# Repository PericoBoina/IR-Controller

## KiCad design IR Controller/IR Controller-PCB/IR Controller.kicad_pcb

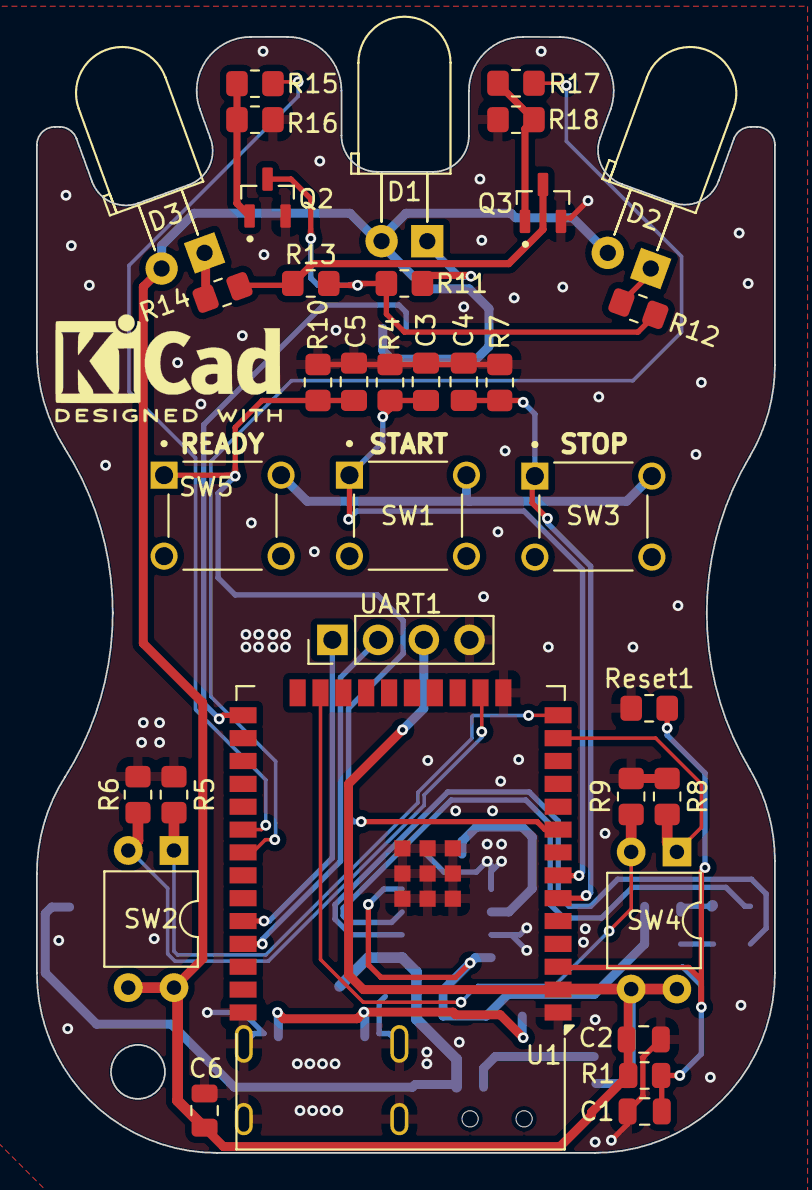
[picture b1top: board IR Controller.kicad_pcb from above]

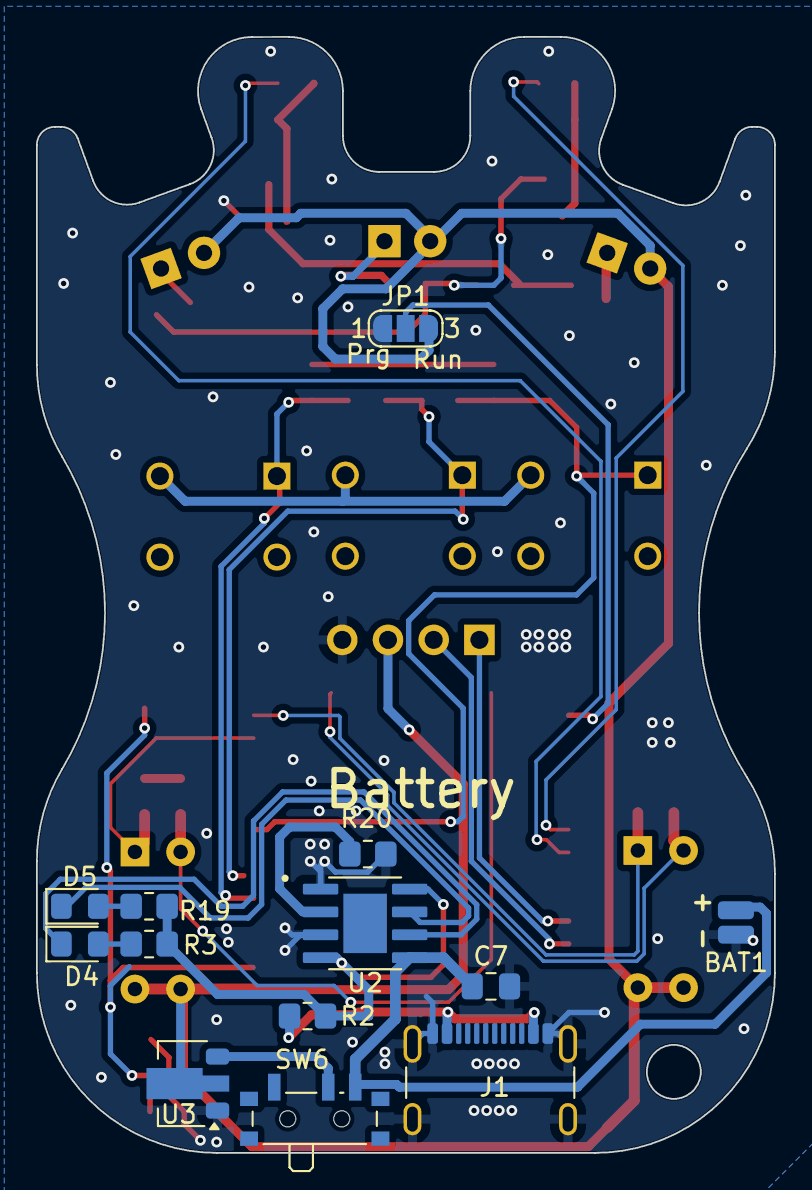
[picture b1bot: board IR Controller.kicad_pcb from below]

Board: 2 copper layers, 41.0 x 62.0 mm, 48 parts (13 on the bottom side), 32 nets.

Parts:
BAT1: 3.7V; SolderWirePad_1x01_SMD_1x2mm
C1: 0.1uF; C_0805_2012Metric
C2, C6: 1uF; C_0805_2012Metric
C3, C4, C5: 0.1uF; C_0805_2012Metric_Pad1.18x1.45mm_HandSolder
C7: 10uF; C_0805_2012Metric_Pad1.18x1.45mm_HandSolder
D1, D2, D3: LED; LED_D5.0mm_Horizontal_O3.81mm_Z15.0mm
D4, D5: LED; LED_0805_2012Metric_Pad1.15x1.40mm_HandSolder
J1: USB_C_Receptacle_USB2.0_16P; USB_C_Receptacle_GCT_USB4105-xx-A_16P_TopMnt_Horizontal
JP1: Jumper_3_Open; SolderJumper-3_P1.3mm_Open_RoundedPad1.0x1.5mm_NumberLabels
Q2, Q3: IRLML2502; SOT23(IRLML2502)
R1: 10K; R_0805_2012Metric
R2, R13: 0r; R_0805_2012Metric_Pad1.20x1.40mm_HandSolder
R3, R11, R12, R14, R19: 150r; R_0805_2012Metric_Pad1.20x1.40mm_HandSolder
R4, R5, R6, R7, R8, R9, R10: 47K; R_0805_2012Metric_Pad1.20x1.40mm_HandSolder
R15, R17: 4.7k; R_0805_2012Metric_Pad1.20x1.40mm_HandSolder
R16, R18: 100K; R_0805_2012Metric_Pad1.20x1.40mm_HandSolder
R20: 1K5; R_0805_2012Metric_Pad1.20x1.40mm_HandSolder
Reset1: Reset; R_0805_2012Metric_Pad1.20x1.40mm_HandSolder
SW1, SW3, SW5: SW_Push; Switch
SW2, SW4: SW_DIP_x02; DIP-4_W7.62mm
SW6: SW_DPDT_x2; SW_SPDT_PCM12
U1: ESP32-WROOM-32D
U2: SOP-8-EP
U3: AMS1117-3.3; SOT-89-3
UART1: Conn_01x04_Pin; PinHeader_1x04_P2.54mm_Vertical

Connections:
5V: R2.2, R3.1, R19.1, U2.4 (VCC), U2.8 (CE)
+3.3V: SW1.2, SW3.2, SW5.2
+3V3: C2.1, C6.1, D1.2 (A), D2.2 (A), D3.2 (A), JP1.3 (B), R1.1, SW2.3, SW2.4, SW4.3, SW4.4, U1.2 (VDD), U3.2 (VO), UART1.3
/ESP_Boot: JP1.2 (C), U1.25 (IO0)
/ESP_En: C1.1, R1.2, Reset1.2, U1.3 (EN)
/Esp32_UART_RX: U1.34 (RXD0/IO3), UART1.1
/Esp32_UART_TX: U1.35 (TXD0/IO1), UART1.2
/LED_IR: R15.2, U1.30 (IO18)
/LED_PROG: R17.2, U1.31 (IO19)
/READY_BTN: C5.1, R10.1, SW5.1, U1.9 (IO33)
/START_BTN: C3.1, R4.1, SW1.1, U1.7 (IO35)
/STOP_BTN: C4.1, R7.1, SW3.1, U1.6 (IO34)
/SWITCH1: R5.1, SW2.1, U1.14 (IO12)
/SWITCH2: R6.1, SW2.2, U1.16 (IO13)
/SWITCH3: R8.1, SW4.1, U1.13 (IO14)
/SWITCH4: R9.1, SW4.2, U1.23 (IO15)
GND: BAT1.2 (-), C1.2, C2.2, C3.2, C4.2, C5.2, C6.2, C7.2, J1.A1 (GND), J1.A12 (GND), J1.B1 (GND), J1.B12 (GND), J1.S1 (SHIELD), JP1.1 (A), Q2.2, Q3.2, R4.2, R5.2, R6.2, R7.2, R8.2, R9.2, R10.2, R16.2, R18.1, R20.1, Reset1.1, U1.1 (GND), U1.15 (GND), U1.38 (GND), U1.39 (GND), U2.1 (Temp), U2.3 (GND), U3.1 (GND), UART1.4
unnamed: BAT1.1 (+), C7.1, SW6.3 (C), U2.5 (BAT)
unnamed: D1.1 (K), R11.1
unnamed: D2.1 (K), R12.1
unnamed: D3.1 (K), R14.1
unnamed: D4.2 (A), R3.2
unnamed: D4.1 (K), U2.6 (Stdby)
unnamed: D5.2 (A), R19.2
unnamed: D5.1 (K), U2.7 (Chrg)
unnamed: J1.A4 (VBUS), J1.A9 (VBUS), J1.B4 (VBUS), J1.B9 (VBUS), R2.1
unnamed: Q2.1, R15.1, R16.1
unnamed: Q2.3, R11.2, R12.2, R13.1
unnamed: Q3.1, R17.1, R18.2
unnamed: Q3.3, R13.2, R14.2
unnamed: SW6.2 (B), U3.3 (VI)
unnamed: R20.2, U2.2 (Prog)
